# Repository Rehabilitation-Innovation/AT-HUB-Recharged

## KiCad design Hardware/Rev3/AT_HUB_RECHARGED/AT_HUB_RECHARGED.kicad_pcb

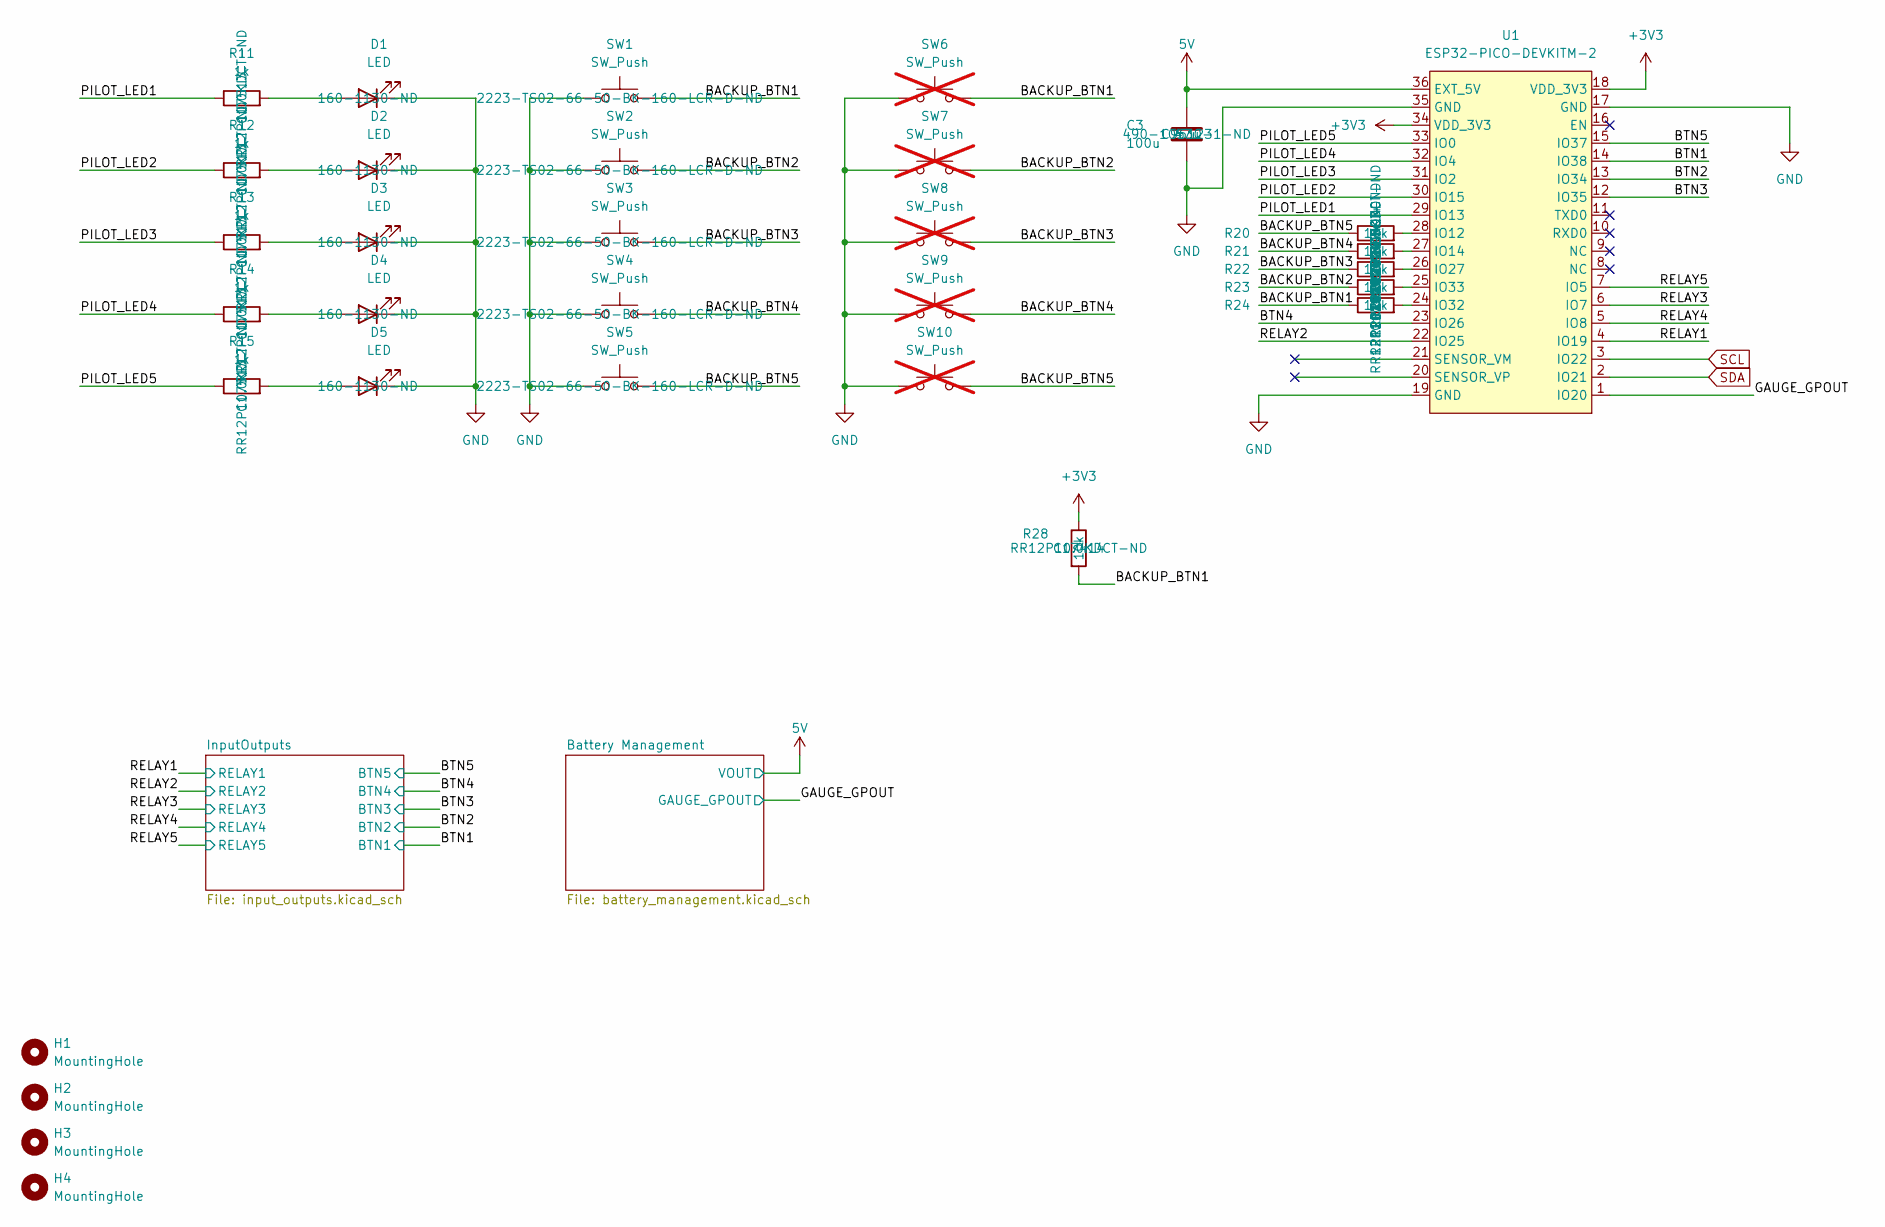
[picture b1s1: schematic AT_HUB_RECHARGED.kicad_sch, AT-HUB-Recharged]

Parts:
C3: 100u; C_1206_3216Metric; LCSC C96123
D1, D2, D3, D4, D5: LED; LED_D5.0mm
H1, H2, H3, H4: MountingHole; MountingHole_3.2mm_M3_Pad_Via
R11, R12, R13, R14, R15: 1k; R_0805_2012Metric; LCSC C17513
R20, R21, R22, R23, R24, R28: 10k; R_0805_2012Metric; LCSC C17414
SW1, SW2, SW3, SW4, SW5: SW_Push; SW_PUSH_6mm
SW6, SW7, SW8, SW9, SW10: SW_Push; SW_800AWSP9M2QE; not fitted
U1: ESP32-PICO-DEVKITM-2; XCVR_ESP32-PICO-KIT-V4.1

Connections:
5V: C3.1, U1.36 (EXT_5V); also elsewhere on the board
+3V3: R28.1, U1.18 (VDD_3V3), U1.34 (VDD_3V3); also elsewhere on the board
/BACKUP_BTN1: R24.1, R28.2, SW1.2, SW6.2
/BACKUP_BTN2: R23.1, SW2.2, SW7.2
/BACKUP_BTN3: R22.1, SW3.2, SW8.2
/BACKUP_BTN4: R21.1, SW4.2, SW9.2
/BACKUP_BTN5: R20.1, SW5.2, SW10.2
/BTN1: U1.14 (IO38); also elsewhere on the board
/BTN2: U1.13 (IO34); also elsewhere on the board
/BTN3: U1.12 (IO35); also elsewhere on the board
/BTN4: U1.23 (IO26); also elsewhere on the board
/BTN5: U1.15 (IO37); also elsewhere on the board
/GAUGE_GPOUT: U1.1 (IO20); also elsewhere on the board
/PILOT_LED1: R11.1, U1.29 (IO13)
/PILOT_LED2: R12.1, U1.30 (IO15)
/PILOT_LED3: R13.1, U1.31 (IO2)
/PILOT_LED4: R14.1, U1.32 (IO4)
/PILOT_LED5: R15.1, U1.33 (IO0)
/RELAY1: U1.4 (IO19); also elsewhere on the board
/RELAY2: U1.22 (IO25); also elsewhere on the board
/RELAY3: U1.6 (IO7); also elsewhere on the board
/RELAY4: U1.5 (IO8); also elsewhere on the board
/RELAY5: U1.7 (IO5); also elsewhere on the board
GND: C3.2, D1.1 (K), D2.1 (K), D3.1 (K), D4.1 (K), D5.1 (K), SW1.1, SW2.1, SW3.1, SW4.1, SW5.1, SW6.1, SW7.1, SW8.1, SW9.1, SW10.1, U1.17 (GND), U1.19 (GND), U1.35 (GND); also elsewhere on the board
unnamed: D1.2 (A), R11.2
unnamed: D2.2 (A), R12.2
unnamed: D3.2 (A), R13.2
unnamed: D4.2 (A), R14.2
unnamed: D5.2 (A), R15.2
unnamed: R20.2, U1.28 (IO12)
unnamed: R21.2, U1.27 (IO14)
unnamed: R22.2, U1.26 (IO27)
unnamed: R24.2, U1.24 (IO32)
unnamed: R23.2, U1.25 (IO33)
SCL: U1.3 (IO22); also elsewhere on the board
SDA: U1.2 (IO21); also elsewhere on the board

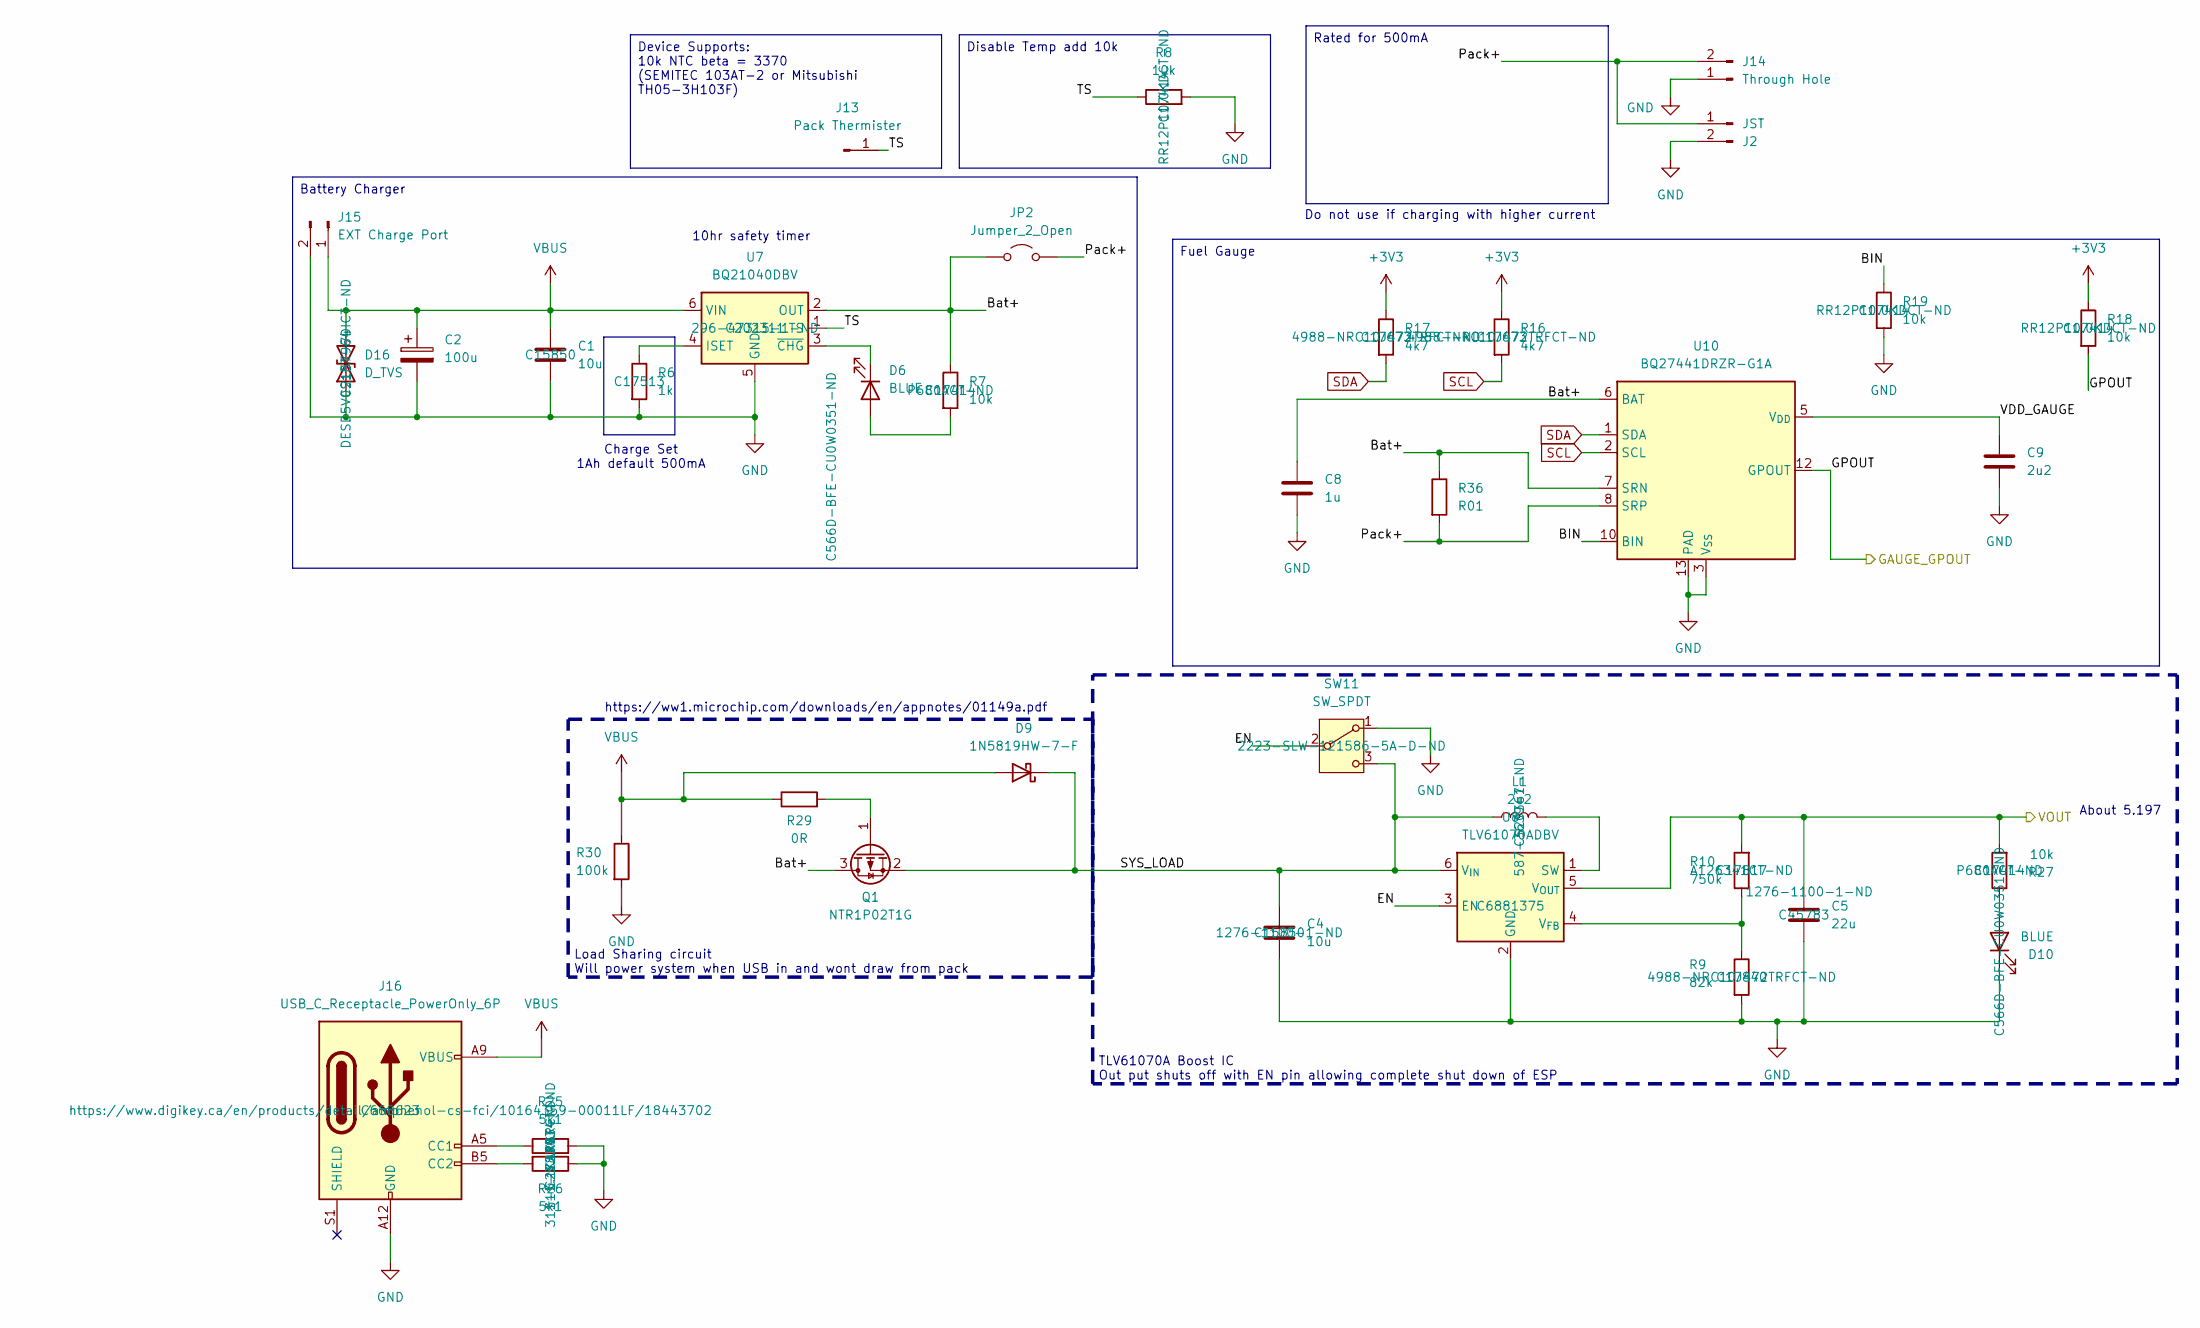
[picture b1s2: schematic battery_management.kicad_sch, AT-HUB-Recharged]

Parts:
C1, C4: 10u; C_0805_2012Metric; LCSC C15850
C2: 100u; CP_EIA-3216-18_Kemet-A
C5: 22u; C_0805_2012Metric; LCSC C45783
C8: 1u; C_0805_2012Metric; LCSC C377773
C9: 2u2; C_0805_2012Metric; LCSC C377773
D6, D10: BLUE; LED_D5.0mm
D9: 1N5819HW-7-F; D_SOD-123; LCSC C82544
D16: D_TVS; D_SOD-323_HandSoldering; LCSC C2157964
J2: JST; JST_PH_B2B-PH-K_1x02_P2.00mm_Vertical
J13: Pack Thermister; PinHeader_1x01_P2.54mm_Vertical
J14: Through Hole; PinHeader_1x02_P2.54mm_Vertical
J15: EXT Charge Port; PinHeader_1x02_P2.54mm_Vertical
J16: USB_C_Receptacle_PowerOnly_6P; USB_C_Receptacle_HRO_TYPE-C-31-M-17; LCSC C668623
JP2: Jumper_2_Open; SolderJumper-2_P1.3mm_Open_RoundedPad1.0x1.5mm
L1: 2u2; Ceaiya SMD,6x6mm CR6028-2R2N; LCSC C520367
Q1: NTR1P02T1G; SOT-23; LCSC C129192
R6: 1k; R_0805_2012Metric; LCSC C17513
R7, R8, R18, R19, R27: 10k; R_0805_2012Metric; LCSC C17414
R9: 82k; R_0805_2012Metric; LCSC C17840
R10: 750k; R_0805_2012Metric; LCSC C17817
R16, R17: 4k7; R_0805_2012Metric; LCSC C17673
R25, R26: 5k1; R_0805_2012Metric; LCSC C27834
R29: 0R; R_0805_2012Metric; LCSC C17477
R30: 100k; R_0805_2012Metric; LCSC C149504
R36: R01; R_0805_2012Metric; LCSC C163089
SW11: SW_SPDT; SW_SLW-121586-5A-D
U7: BQ21040DBV; SOT-23-6; LCSC C202311
U8: TLV61070ADBV; SOT-23-6; LCSC C6881375
U10: BQ27441DRZR-G1A; Texas_S-PDSO-N12; LCSC C473397

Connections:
5V: C5.1, R10.2, R27.2, U8.5 (V_{OUT}); also elsewhere on the board
+3V3: R16.1, R17.1, R18.1; also elsewhere on the board
/Battery Management/BIN: R19.1, U10.10 (BIN)
/Battery Management/Bat+: C8.1, JP2.1 (A), Q1.3 (D), R7.1, R36.1, U7.2 (OUT), U10.6 (BAT), U10.7 (SRN)
/Battery Management/EN: SW11.2 (B), U8.3 (EN)
/Battery Management/Pack+: J2.1, J14.2, JP2.2 (B), R36.2, U10.8 (SRP)
/Battery Management/SYS_LOAD: C4.1, D9.1 (K), L1.1, Q1.2 (S), SW11.3 (C), U8.6 (V_{IN})
/Battery Management/TS: J13.1, R8.1, U7.1 (TS)
/Battery Management/VDD_GAUGE: C9.1, U10.5 (V_{DD})
/GAUGE_GPOUT: R18.2, U10.12 (GPOUT); also elsewhere on the board
GND: C1.2, C2.2, C4.2, C5.2, C8.2, C9.2, D10.1 (K), D16.1 (A1), J2.2, J14.1, J15.2, J16.A12 (GND), J16.B12 (GND), R6.2, R8.2, R9.2, R19.2, R25.2, R26.1, R30.2, SW11.1 (A), U7.5 (GND), U8.2 (GND), U10.3 (V_{SS}), U10.13 (PAD); also elsewhere on the board
unnamed: D6.2 (A), R7.2
unnamed: D6.1 (K), U7.3 (~CHG)
unnamed: D10.2 (A), R27.1
unnamed: J16.A5 (CC1), R25.1
unnamed: J16.B5 (CC2), R26.2
unnamed: Q1.1 (G), R29.2
unnamed: R6.1, U7.4 (ISET)
unnamed: L1.2, U8.1 (SW)
unnamed: R9.1, R10.1, U8.4 (V_{FB})
SCL: R16.2, U10.2 (SCL); also elsewhere on the board
SDA: R17.2, U10.1 (SDA); also elsewhere on the board
VBUS: C1.1, C2.1, D9.2 (A), D16.2 (A2), J15.1, J16.A9 (VBUS), J16.B9 (VBUS), R29.1, R30.1, U7.6 (VIN)

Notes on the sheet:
Load Sharing circuit Will power system when USB in and wont draw from pack
10hr safety timer
About 5.197
Do not use if charging with higher current
TLV61070A Boost IC Out put shuts off with EN pin allowing complete shut down of ESP
https://ww1.microchip.com/downloads/en/appnotes/01149a.pdf
Charge Set 1Ah default 500mA
Fuel Gauge
Device Supports: 10k NTC beta = 3370 (SEMITEC 103AT-2 or Mitsubishi TH05-3H103F)
Disable Temp add 10k
Battery Charger
Rated for 500mA

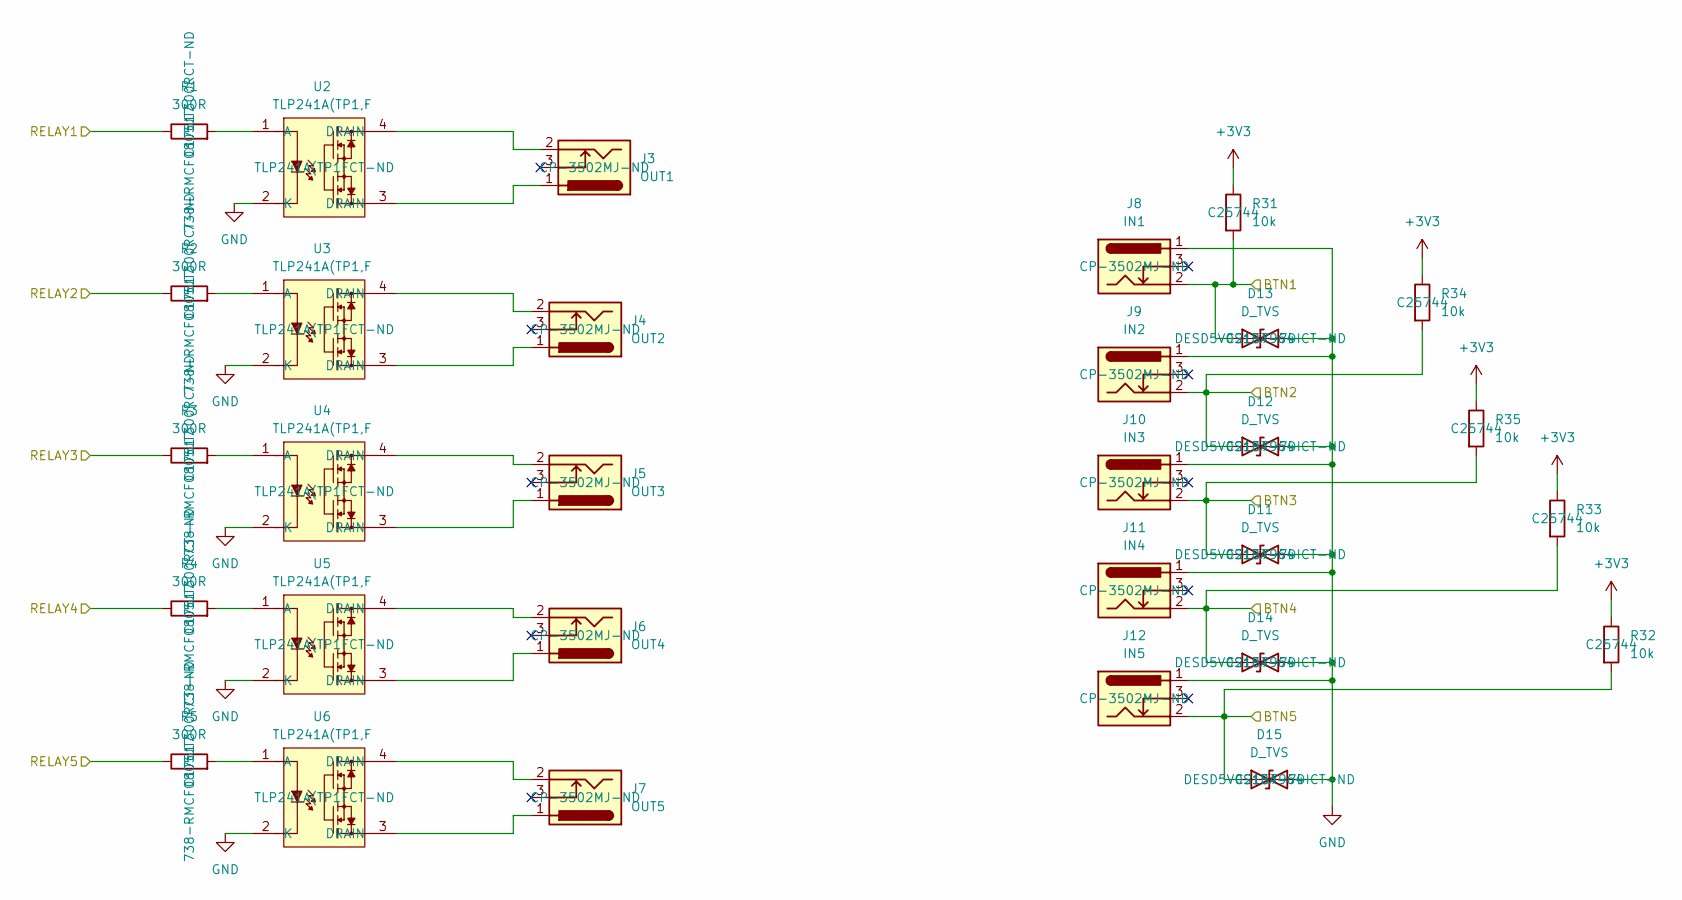
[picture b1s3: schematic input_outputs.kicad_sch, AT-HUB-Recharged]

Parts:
D11, D12, D13, D14, D15: D_TVS; D_SOD-323_HandSoldering; LCSC C2157964
J3: OUT1; CUI_MJ-3502
J4: OUT2; CUI_MJ-3502
J5: OUT3; CUI_MJ-3502
J6: OUT4; CUI_MJ-3502
J7: OUT5; CUI_MJ-3502
J8: IN1; CUI_MJ-3502
J9: IN2; CUI_MJ-3502
J10: IN3; CUI_MJ-3502
J11: IN4; CUI_MJ-3502
J12: IN5; CUI_MJ-3502
R1, R2, R3, R4, R5: 300R; R_0805_2012Metric; LCSC C17617
R31, R32, R33, R34, R35: 10k; R_0402_1005Metric; LCSC C25744
U2, U3, U4, U5, U6: TLP241A(TP1,F; 11-5B201S_TOS

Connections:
+3V3: R31.1, R32.1, R33.1, R34.1, R35.1; also elsewhere on the board
/BTN1: D13.1 (A1), J8.2, R31.2; also elsewhere on the board
/BTN2: D12.1 (A1), J9.2, R34.2; also elsewhere on the board
/BTN3: D11.1 (A1), J10.2, R35.2; also elsewhere on the board
/BTN4: D14.1 (A1), J11.2, R33.2; also elsewhere on the board
/BTN5: D15.1 (A1), J12.2, R32.2; also elsewhere on the board
/RELAY1: R1.1; also elsewhere on the board
/RELAY2: R2.1; also elsewhere on the board
/RELAY3: R3.1; also elsewhere on the board
/RELAY4: R4.1; also elsewhere on the board
/RELAY5: R5.1; also elsewhere on the board
GND: D11.2 (A2), D12.2 (A2), D13.2 (A2), D14.2 (A2), D15.2 (A2), J8.1, J9.1, J10.1, J11.1, J12.1, U2.2 (K), U3.2 (K), U4.2 (K), U5.2 (K), U6.2 (K); also elsewhere on the board
unnamed: J3.1, U2.3 (DRAIN)
unnamed: J3.2, U2.4 (DRAIN)
unnamed: J4.1, U3.3 (DRAIN)
unnamed: J4.2, U3.4 (DRAIN)
unnamed: J5.1, U4.3 (DRAIN)
unnamed: J5.2, U4.4 (DRAIN)
unnamed: J6.1, U5.3 (DRAIN)
unnamed: J6.2, U5.4 (DRAIN)
unnamed: J7.1, U6.3 (DRAIN)
unnamed: J7.2, U6.4 (DRAIN)
unnamed: R1.2, U2.1 (A)
unnamed: R2.2, U3.1 (A)
unnamed: R3.2, U4.1 (A)
unnamed: R4.2, U5.1 (A)
unnamed: R5.2, U6.1 (A)

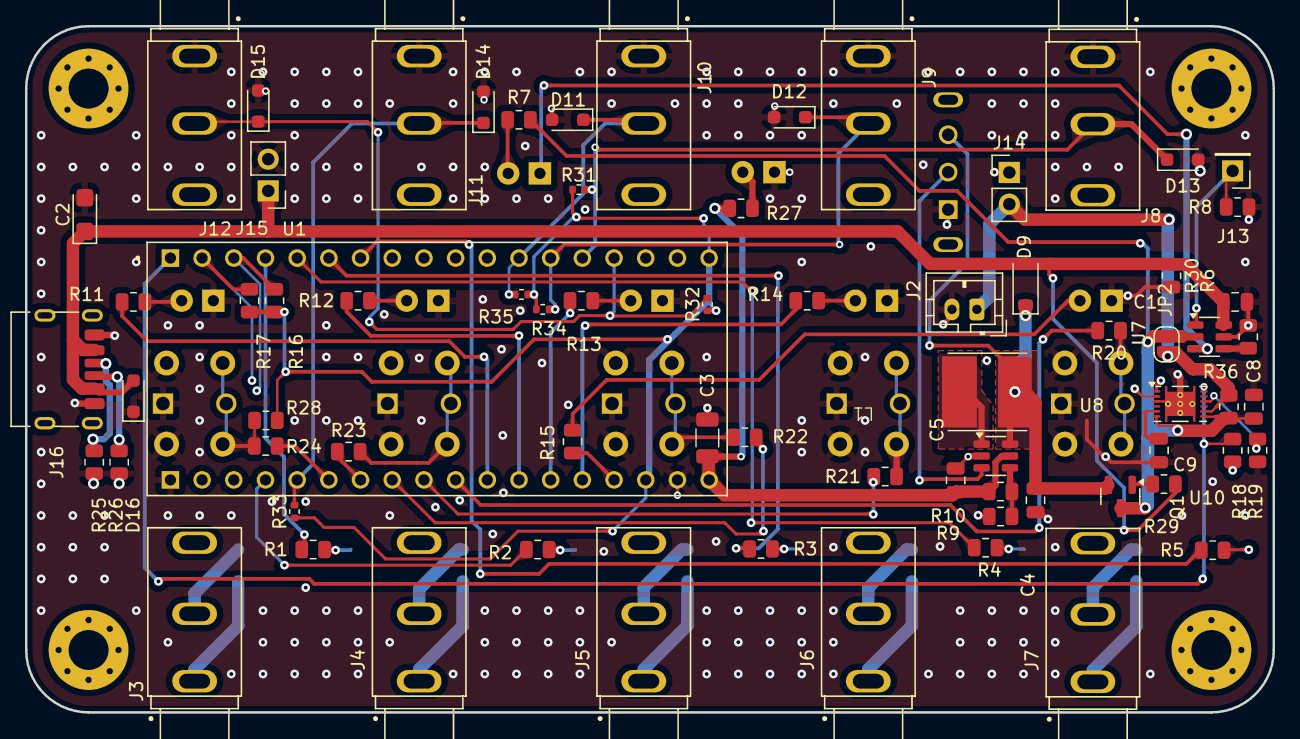
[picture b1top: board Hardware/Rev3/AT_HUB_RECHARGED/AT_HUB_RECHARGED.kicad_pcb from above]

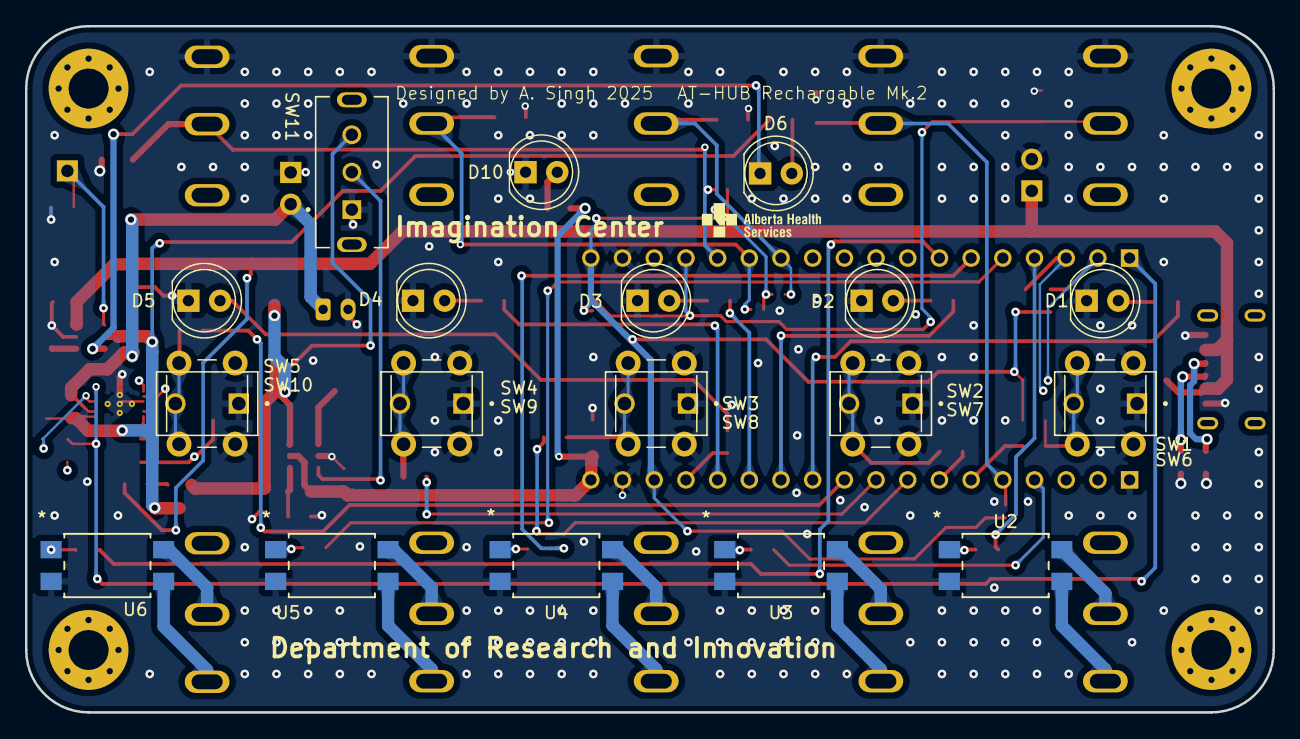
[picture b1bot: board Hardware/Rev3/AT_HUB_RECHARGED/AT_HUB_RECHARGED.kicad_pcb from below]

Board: 4 copper layers, 100.0 x 55.0 mm, 99 parts (23 on the bottom side), 68 nets.

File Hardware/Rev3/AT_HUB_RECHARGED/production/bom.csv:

Designator,Footprint,Quantity,Value,LCSC Part #
"C1, C4",0805,2,10u,C15850
C2,CP_EIA-3216-18_Kemet-A,1,100u,
C3,1206,1,100u,C96123
C5,0805,1,22u,C45783
C8,0805,1,1u,C377773
C9,0805,1,2u2,C377773
"D1, D2, D3, D4, D5",LED_D5.0mm,5,LED,
"D10, D6",LED_D5.0mm,2,BLUE,
"D11, D12, D13, D14, D15, D16",D_SOD-323_HandSoldering,6,D_TVS,C2157964
D9,D_SOD-123,1,1N5819HW-7-F,C82544
J10,CUI_MJ-3502,1,IN3,
J11,CUI_MJ-3502,1,IN4,
J12,CUI_MJ-3502,1,IN5,
J13,PinHeader_1x01_P2.54mm_Vertical,1,Pack Thermister,
J14,PinHeader_1x02_P2.54mm_Vertical,1,Through Hole,
J15,PinHeader_1x02_P2.54mm_Vertical,1,EXT Charge Port,
J16,USB_C_Receptacle_HRO_TYPE-C-31-M-17,1,USB_C_Receptacle_PowerOnly_6P,C668623
J2,JST_PH_B2B-PH-K_1x02_P2.00mm_Vertical,1,JST,
J3,CUI_MJ-3502,1,OUT1,
J4,CUI_MJ-3502,1,OUT2,
J5,CUI_MJ-3502,1,OUT3,
J6,CUI_MJ-3502,1,OUT4,
J7,CUI_MJ-3502,1,OUT5,
J8,CUI_MJ-3502,1,IN1,
J9,CUI_MJ-3502,1,IN2,
JP2,SolderJumper-2_P1.3mm_Open_RoundedPad1.0x1.5mm,1,Jumper_2_Open,
JP3,SolderJumper-2_P1.3mm_Open_RoundedPad1.0x1.5mm,1,SKIP PMOS 2,
L1,"Ceaiya SMD,6x6mm CR6028-2R2N",1,2u2,C520367
"Q1, Q2",SOT-23,2,NTR1P02T1G,C129192
"R1, R2, R3, R4, R5",0805,5,300R,C17617
R10,0805,1,15k,C17475
"R11, R12, R13, R14, R15, R18, R19, R20, R21, R22, R23, R24, R8",0805,13,10k,C17414
"R16, R17, R9",0805,3,4k7,C17673
"R25, R26",0805,2,5k1,C27834
"R27, R6, R7",0805,3,1k,C17513
R29,0805,1,0R,C17477
R30,0805,1,100k,C149504
"R31, R32, R33, R34, R35",0402,5,10k,C25744
R36,0805,1,R01,C163089
"SW1, SW2, SW3, SW4, SW5",SW_PUSH_6mm,5,SW_Push,
"SW10, SW6, SW7, SW8, SW9",SW_800AWSP9M2QE,5,SW_Push,
SW11,SW_SLW-121586-5A-D,1,SW_SPDT,
U1,XCVR_ESP32-PICO-KIT-V4.1,1,ESP32-PICO-DEVKITM-2,
U10,Texas_S-PDSO-N12,1,BQ27441DRZR-G1A,C473397
"U2, U3, U4, U5, U6",11-5B201S_TOS,5,"TLP241A(TP1,F",
U7,SOT-23-6,1,BQ21040DBV,C202311
U8,SOT-23-6,1,TLV61070ADBV,C6881375

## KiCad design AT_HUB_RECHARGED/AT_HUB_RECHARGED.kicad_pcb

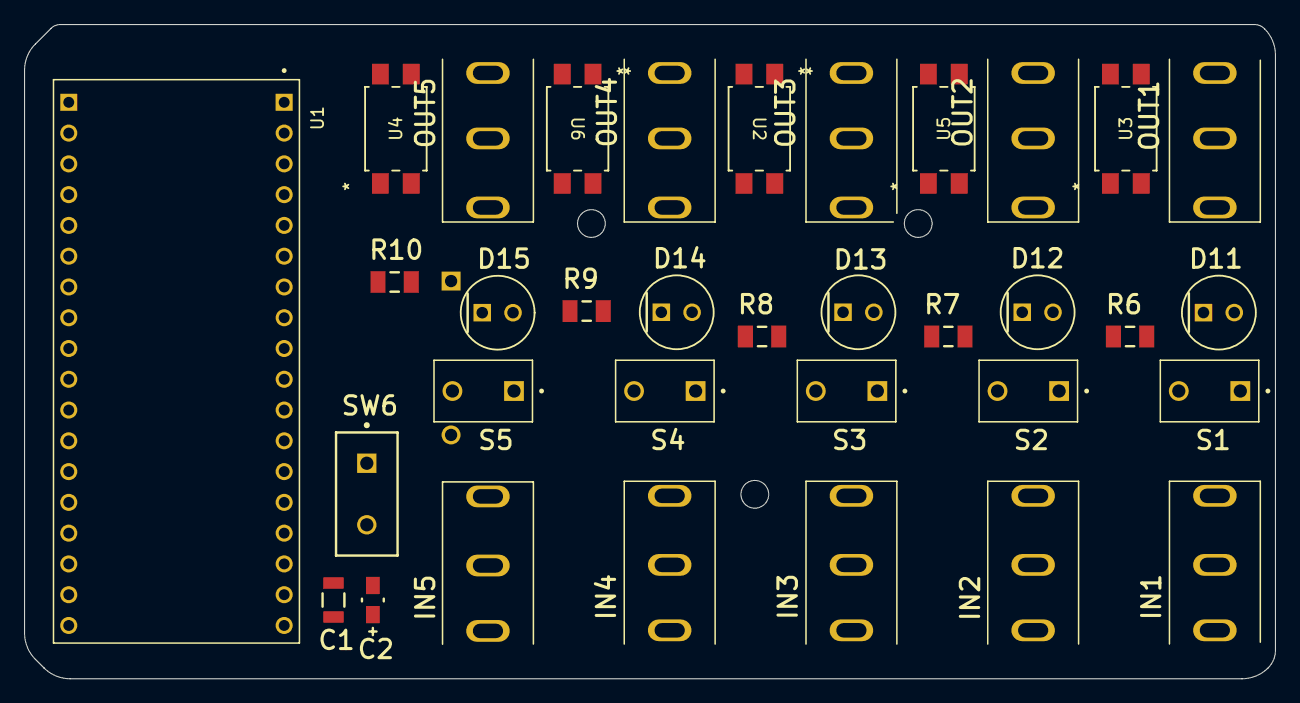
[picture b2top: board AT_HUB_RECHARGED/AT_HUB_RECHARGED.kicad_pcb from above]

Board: 2 copper layers, 103.3 x 54.0 mm, 35 parts (1 on the bottom side), 8 nets, no tracks yet.

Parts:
BT1: BH9VPC; FP-BH9VPC-MFG
C1: C1206C104K4RACTU; FP-C1206C-EB-MFG
C2: T491A106M016AT; FP-T491A106M016AT-MFG
D11, D12, D13, D14, D15: HLMP-4700; FP-HLMP-4700-MFG
IN1, IN2, IN3, IN4, IN5: MJ-3502; CUI_MJ-3502
OUT1, OUT2, OUT3, OUT4, OUT5: MJ-3502; CUI_MJ-3502
R6, R7, R8, R9, R10: CRCW1206750RFKEAHP; RESC3116X65X50NL20T20
S1, S2, S3, S4, S5: 800AWSP9M2QE; SW_800AWSP9M2QE
SW6: TS02CBE; CKCP-TS02CBE_V
U1: ESP32-PICO-DEVKITM-2; XCVR_ESP32-PICO-KIT-V4.1
U2, U3, U4, U5, U6: TLP241A(TP1,F; 11-5B201S_TOS

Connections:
GND: BT1.1, C1.2, C2.1, D11.1, D12.1, D13.1, D14.1, D15.1, IN1.1, IN2.1, IN3.1, IN4.1, IN5.1, S1.1, S2.1, S3.1, S4.1, S5.1, U2.2 (K), U3.2 (K), U4.2 (K), U5.2 (K), U6.2 (K)
NetBT1_2: BT1.2, SW6.1
NetD11_2: D11.2, R6.2
NetD12_2: D12.2, R7.2
NetD13_2: D13.2, R8.2
NetD14_2: D14.2, R9.2
NetD15_2: D15.2, R10.2
VIN: C1.1, C2.2, SW6.3

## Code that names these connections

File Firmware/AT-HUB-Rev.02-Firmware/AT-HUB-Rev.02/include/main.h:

#pragma once
#include <BluetoothSerial.h>
#define BLUETOOTH_HANDLER_CORE 1
#define BLUETOOTH_TASK_PRIORITY 0
#define INPUT_TASK_PRIORITY 0
#define INPUT_HANDLER_CORE 0

#define BTN1 22
#define BTN2 19
#define BTN3 8
#define BTN4 0
#define BTN5 4

#define BACKUP_BTN1 2
#define BACKUP_BTN2 15
#define BACKUP_BTN3 13
#define BACKUP_BTN4 12
#define BACKUP_BTN5 14

#define LED1 27
#define LED2 33
#define LED3 32
#define LED4 26
#define LED5 25

#define RELAY1 20
#define RELAY2 21
#define RELAY3 7
#define RELAY4 5
#define RELAY5 3

// button state machine.
typedef enum
{
    BUTTON_UNPRESSED = 0,
    BUTTON_PRESSED = 1,
    BUTTON_DOUBLE_PRESSED = 2,
    BUTTON_HELD = 3,
    BUTTON_RELEASD = 4 // probably wont use but here just in case.
} Button_State_t;

// stores global state and can keep presistance for multiple button presses at the same time.
typedef struct
{
    Button_State_t input_1;
    Button_State_t input_2;
    Button_State_t input_3;
    Button_State_t input_4;
    Button_State_t input_5;

    int output1;
    int output2;
    int output3;
    int output4;
    int output5;

} AT_HUB_Input_Ouput_States_t;

typedef enum
{
    AT_HUB_INPUT_1 = BTN1,
    AT_HUB_INPUT_2 = BTN2,
    AT_HUB_INPUT_3 = BTN3,
    AT_HUB_INPUT_4 = BTN4,
    AT_HUB_INPUT_5 = BTN5,

} AT_HUB_Inputs_t;

typedef enum
{
    AT_HUB_OUTPUT_1 = RELAY1,
    AT_HUB_OUTPUT_2 = RELAY2,
    AT_HUB_OUTPUT_3 = RELAY3,
    AT_HUB_OUTPUT_4 = RELAY4,
    AT_HUB_OUTPUT_5 = RELAY5,

} AT_HUB_Outputs_t;

// Input output multiplexer
// This struct defines the variables for what output each input controls.
typedef struct
{
    AT_HUB_Outputs_t in1_controls = AT_HUB_OUTPUT_1; // Ex. assign a output type to this for in 1 to control.
    AT_HUB_Outputs_t in2_controls = AT_HUB_OUTPUT_2;
    AT_HUB_Outputs_t in3_controls = AT_HUB_OUTPUT_3;
    AT_HUB_Outputs_t in4_controls = AT_HUB_OUTPUT_4;
    AT_HUB_Outputs_t in5_controls = AT_HUB_OUTPUT_5;
} AT_HUB_Input_Output_Map_t;

struct OutputStates
{
    int outputrelay_pin;
    int outputled_pin;
    int state_from_bt;
    int backupbutton;
};

typedef struct
{
    BluetoothSerial SerialBT; // Global serial (Safe Access I think LMAO!)
    // AT_HUB_Input_Ouput_States_t *global_input_output_states;
    // AT_HUB_Input_Output_Map_t *global_input_output_mapping;

    OutputStates output1;
    OutputStates output2;
    OutputStates output3;
    OutputStates output4;
    OutputStates output5;
    bool btScanAsync = true;
    bool btScanSync = true;
} AT_HUB_State_t;

#define LOG(x) Serial.println("[" __FILE__ "]" x)

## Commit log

2025-06-05 Added new Boost started new layout verification and cpos
2025-06-13 Added new protections and load sharing for lipo, also changed inductor to be autoplaced
2025-06-16 Changed net label for charging subcircuit to Bat+
2025-06-27 Done the design will verify
2025-07-30 Added Rev 3
2025-08-11 Final working
